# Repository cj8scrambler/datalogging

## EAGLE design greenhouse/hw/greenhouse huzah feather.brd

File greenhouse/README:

This project logs data using an ESP8266 Arduino board to the
adafruit.io MQTT backend for monitoring conditions in greenhouse.

The device runs off of battery with a solar cell connected for
charging.  On sunny summer days it can run on it's own.  On
cold winter cloudy days it needs to be manually recharged every
2 weeks.

The following data is logged:
  * DHT22 - humidity and temperature
  * VEML6070 - Ultraviolet light (discontinued part)
  * BMP388 - Barometric pressure and temperature
  * A/D - Battery voltage

-------------------------------------------------------------
Arduino IDE Setup:

  File->Preferences->Additional Boards Manager URLs: 
  *  https://arduino.esp8266.com/stable/package_esp8266com_index.json
  *  Be sure to install v2.4.2 to avoid issue: https://github.com/esp8266/Arduino/issues/5787

  Install Libraries:
  *  Adafruit Unified Sensor
  *  DHT sensor library
  *  Adafruit IO Arduino
  *  Adafruit BMP3XX Library
  *  Adafruit VEML6075 Library

-------------------------------------------------------------

Or build / upload directly from the command line:

  Install arduino-cli:
  *  curl -fsSL https://raw.githubusercontent.com/arduino/arduino-cli/master/install.sh | BINDIR=~/bin sh

  Configure arduino-cli:
  *  arduino-cli config init
  *  edit ~/.arduino15/arduino-cli.yaml and replace the board_manager line with:
     board_manager:
       additional_urls:
        - http://arduino.esp8266.com/stable/package_esp8266com_index.json
        - https://raw.githubusercontent.com/espressif/arduino-esp32/gh-pages/package_esp32_index.json
  *  arduino-cli core update-index
  *  arduino-cli core search
       List core packages available
  *  arduino-cli core install esp8266:esp8266
  *  arduino-cli board listall
       Set BOARD variable in Makefile to appropriate board (such as 'esp8266:esp8266:huzzah')

  Install dependencies:
  *  arduino-cli lib install "Adafruit IO Arduino"
  *  arduino-cli lib install "DHT sensor library"
  *  arduino-cli lib install "Adafruit Unified Sensor"
  *  arduino-cli lib install "Adafruit BMP3XX Library"
  *  arduino-cli lib install "Adafruit VEML6075 Library"

  Build
  *  make 

  Upload 
  *  make upload        # set serial port path in Makefile

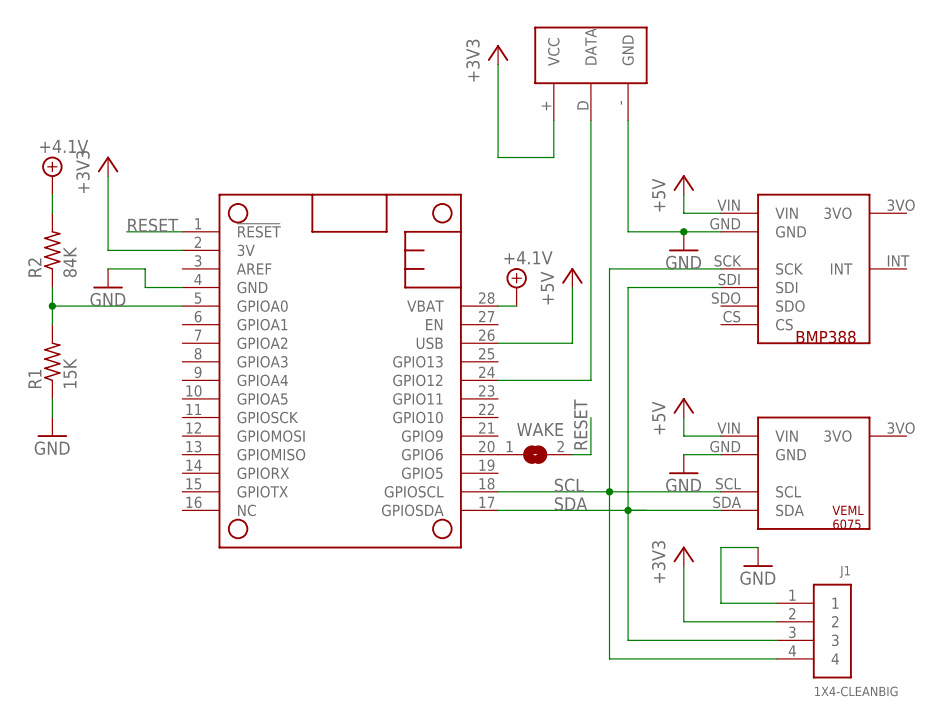
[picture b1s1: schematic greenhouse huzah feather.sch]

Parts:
J1: 1X4-CLEANBIG; 1X04-CLEANBIG
MS1: FEATHERWING
R1: 15K; R0805
R2: 84K; R0805
U$1: ADA_BMP388
U$2: ADA_VEML6075
U$4: DHT11; DHT22_DAUGHTER
WAKE: SJ

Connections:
+3V3: J1.2, MS1.2 (3V), U$4.+ (VCC)
+4.1V: MS1.28 (VBAT), R2.2
+5V: MS1.26 (USB), U$1.VIN, U$2.VIN
GND: J1.1, MS1.4 (GND), R1.1, U$1.GND, U$2.GND, U$4.- (GND)
unnamed: MS1.20 (GPIO6), WAKE.1
unnamed: MS1.5 (GPIOA0), R1.2, R2.1
unnamed: MS1.24 (GPIO12), U$4.D (DATA)
RESET: MS1.1 (!RESET), WAKE.2
SCL: J1.4, MS1.18 (GPIOSCL), U$1.SCK, U$2.SCL
SDA: J1.3, MS1.17 (GPIOSDA), U$1.SDI, U$2.SDA

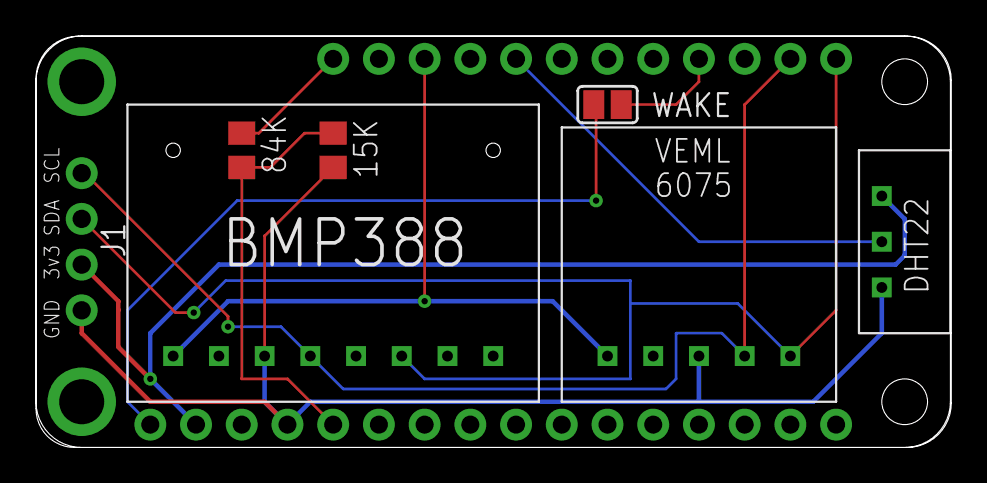
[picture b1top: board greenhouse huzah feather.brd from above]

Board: 2 copper layers, 50.9 x 22.9 mm, 8 parts (0 on the bottom side), 10 nets.

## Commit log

2020-12-15 Add luminary maping script
    Python script to convert data from a Google Sheets spreadsheet
    to a KML file.
2020-12-27 dht to adafruit.io data logger
2020-12-27 Greenhouse logging firmware v1.0
    Log data on ESP8266 Huzzah with the following sensors to adafruit.io:
    VEML6075 - UV sensor (discontinued)
    BMP388 - Temp / Pressure
    DHT22 - Temp / Humidity
2020-12-27 Greenhouse feather daugher board V1.0
    Huzzah feather daughter board to hold sensors.
2020-12-27 Updates for VEML
    Configure with default coeficients; log UV-A and UV-B
2020-12-27 Update batt voltage reading
    Update battery voltage reading on A0 using real resistor divider
    values.
2020-12-27 Update the greenhouse datalogger README
2021-11-23 Updates for 2021
2022-02-10 Tilt Pi Relay
    Add baseline work for a Pi based temp controller which reads Tilt
    Hydrometer data and logs everything to adafruit.io
2022-10-31 Final updates from 2021
2022-12-23 Add a gitignore
2022-12-23 Update to later packages
2023-01-24 Big rewrite - functional
    Functional 2-channel relay based temperature controller for beer
    fermentation. Temperature is sensed and logged from one-wire-bus
    temp sensors. GPIOs turn relays on/off to heat or cool. 3 other
    temperatures are also logged for internal, ambient and glycol.
    A basic UI is implemented with serial LCDs and rotary encoders.
    Any nearby Tilt hyrdometers are also logged from their BLE advertisements.
2023-09-05 tiltPiRelay: Add hardware description
2023-09-16 Cleanup logging, documentation and install
    - Clean up the logging mechanisms so modules can be logged at different
    levels.
    - Fix various comments describing the hardware.
    - Create a script to setup / takedown one-wire busses
    - Create a systemd service to start script at boot
    - Update packages
2023-09-17 Fix initial LCD update when temp sensors missing
2023-09-17 Cleanup shutdown and error handling
    - Make sure everything is turned off at exit.
    - Make systemctl service handle failures more robustly
    - Remove logfile accidently checked in.
2023-09-24 Scale heat/cool values for AIO
    AIO can't do dual Y axis plot, so scale the heat / cool values to
    something closer to the expected temp range so the graph is readable.
